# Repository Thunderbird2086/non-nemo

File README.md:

# 난네모
난네모 (Non Nemo) is an ortholinear 3x5 split keyboard. In Korean, 네모 (nemo) means 'rectangle,' and 난 (non) translates to 'I am.'  So, together, it brings the idea: 'I am a rectangle.'

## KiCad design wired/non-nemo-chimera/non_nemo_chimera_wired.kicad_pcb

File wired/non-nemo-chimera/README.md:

# 선달린 난네모 Chimera

## BOM
| **Component**        | **Quantity** | **Description**  |
|---                   |---:          |---               |
| Xiao RP2040          | 2            | MCU              |
| 1N4148W              | 36           | SMD 1206 SOD-123 |
| MX Hotswap sockets   | 30           | Hotswap sockets compatible with MX switches |
| MX Keyswitches       | 30           | MX compatible keyswitches |
| MX Key caps          | 30           | MX compatible keycaps |
| Choc Hotswap sockets | 6            | Hotswap sockets compatible with Choc switches |
| Choc Keyswitches     | 6            | Choc compatible keyswitches |
| Choc Key caps        | 6            | Choc compatible keycaps |
| PCB                  | 1            | MX Profile      |
| Tactile Push Button  | 2            | SMD 2x4x3.5mm    |
| top plate MX         | 1            | [Chimera](../plates/chimera/) |
| top plate            | 1            | [Chimera](../plates/chimera/) |
| bottom plate         | 1            | [Chimera](../plates/chimera/) |
| M2 screw	           | 32           | M2x5mm          |
| M2 spacer            | 16           | M2x5mm          |
| M2 standoff          | 10           | M2x3mm          |
| Rubber foot          | 8            | 8x3mm           |

## PCB

## Case
### Plates

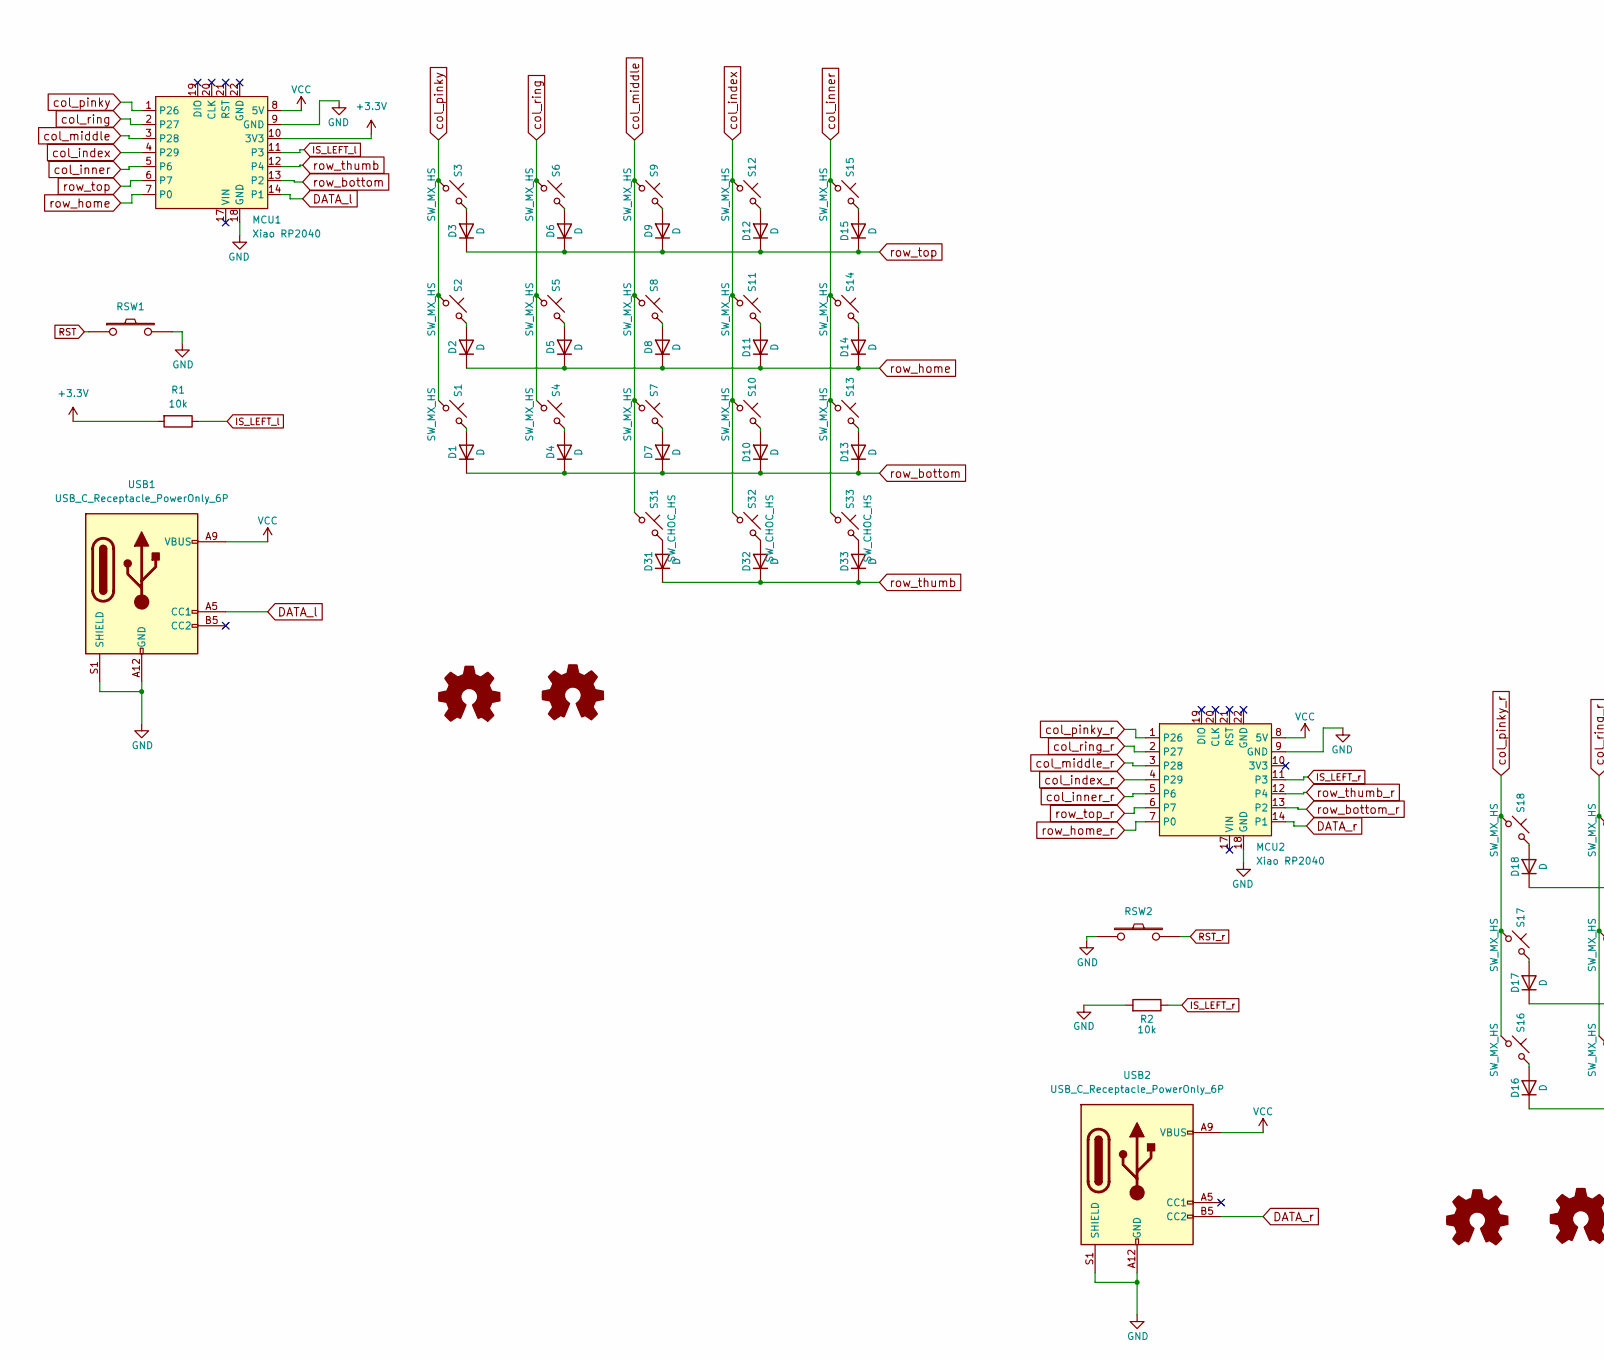
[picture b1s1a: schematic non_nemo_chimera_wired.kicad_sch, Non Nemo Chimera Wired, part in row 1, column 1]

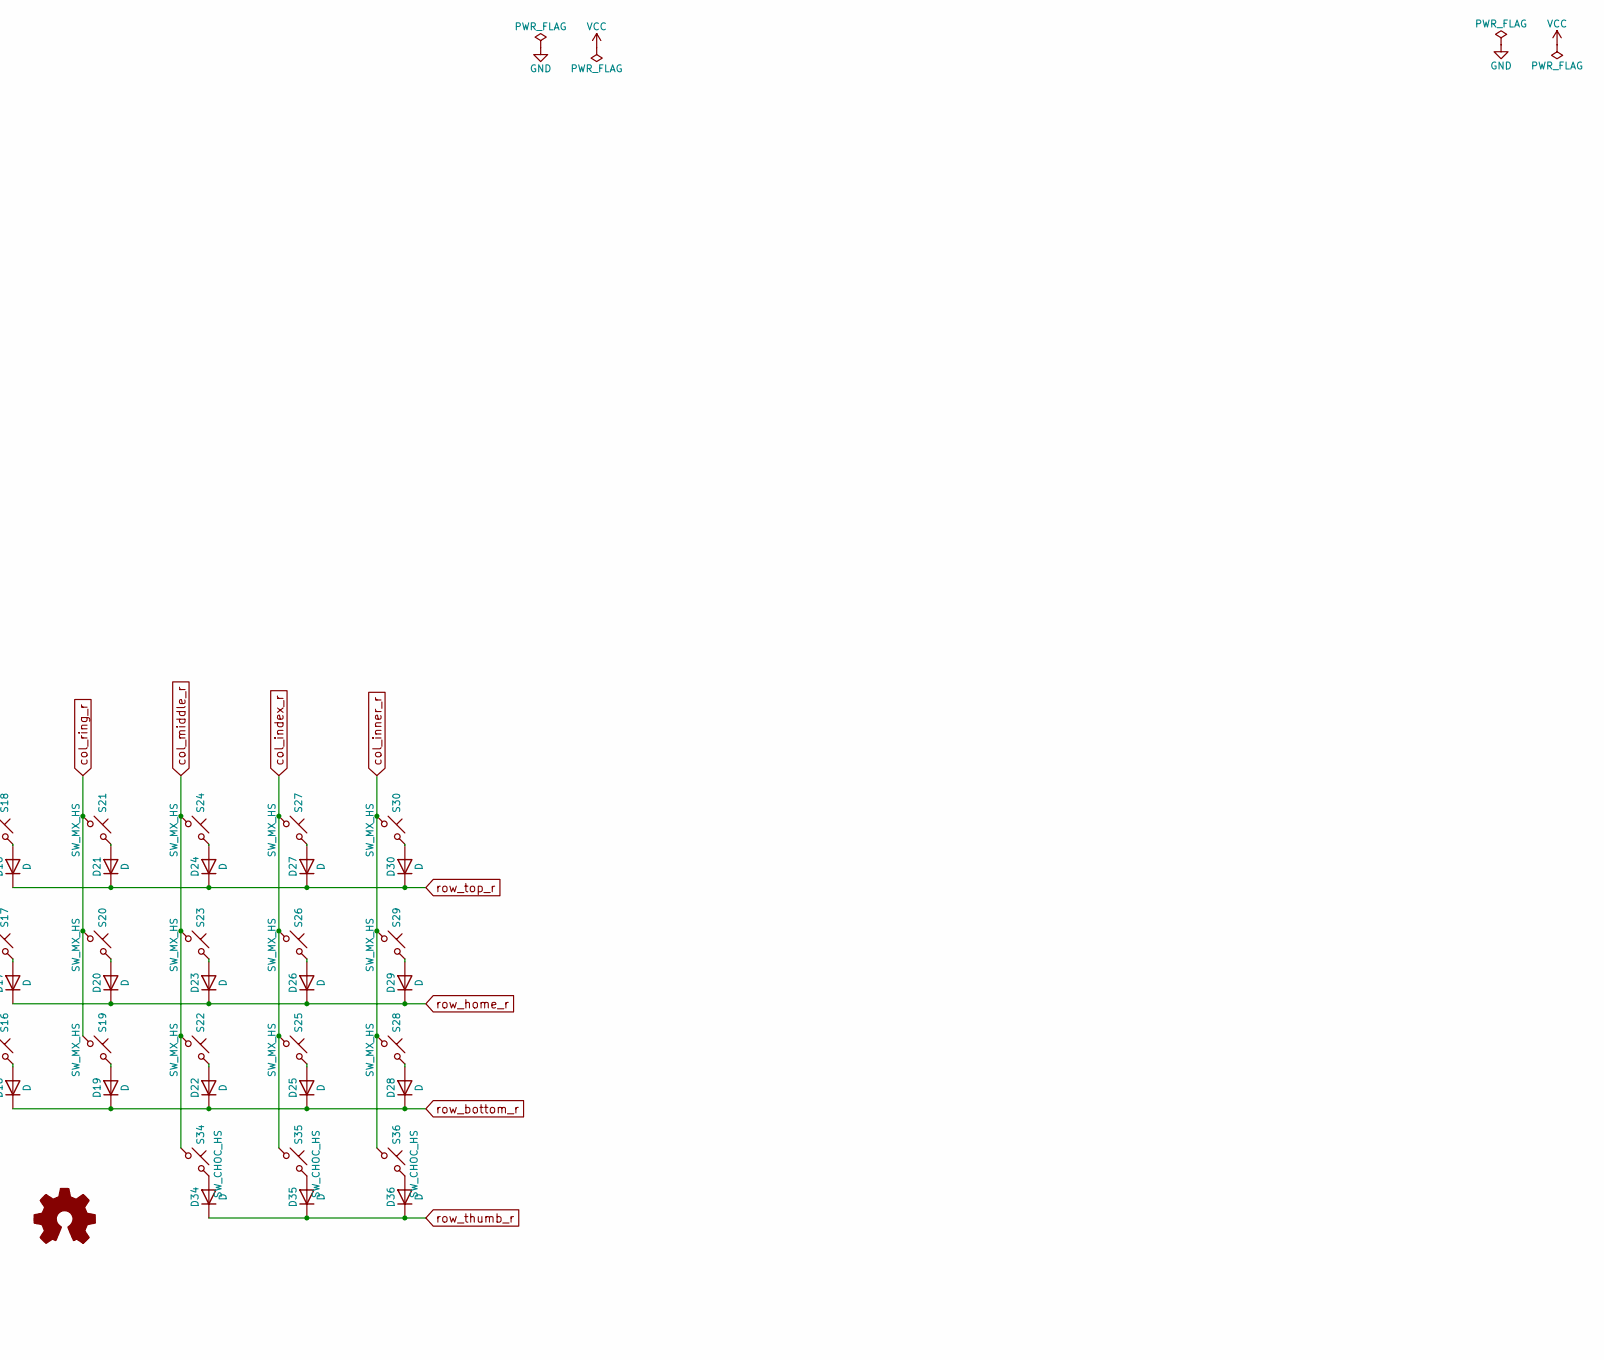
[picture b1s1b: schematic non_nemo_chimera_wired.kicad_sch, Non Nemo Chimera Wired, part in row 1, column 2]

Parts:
D1, D2, D3, D4, D5, D6, D7, D8, D9, D10, D11, D12, D13, D14, D15, D16, D17, D18, D19, D20, D21, D22, D23, D24, D25, D26, D27, D28, D29, D30, D31, D32, D33, D34, D35, D36: D; D3_SMD
LOGO1, LOGO3: Logo_Open_ErgoGen; utility_ergogen_logo
LOGO2, LOGO4: Logo_Open_Hardware_Small; OSHW-Logo_5.7x6mm_SilkScreen
MCU1, MCU2: Xiao RP2040; xiao_rp2040
R1, R2: 10k; R_0805_2012Metric_Pad1.20x1.40mm_HandSolder
RSW1, RSW2: SMT 2X4X3.5MM Tactile Tact Push Button
S1, S2, S3, S4, S5, S6, S7, S8, S9, S10, S11, S12, S13, S14, S15, S16, S17, S18, S19, S20, S21, S22, S23, S24, S25, S26, S27, S28, S29, S30: SW_MX_HS; SW_MX_HS_1u
S31, S32, S33, S34, S35, S36: SW_CHOC_HS; SW_choc_v1_v2_HS_1u
USB1, USB2: USB_C_Receptacle_PowerOnly_6P; USB-20C-F-6C16

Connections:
+3.3V: MCU1.10 (3V3), R1.2
DATA_l: MCU1.14 (P1), USB1.A5 (CC1)
DATA_r: MCU2.14 (P1), USB2.B5 (CC2)
GND: MCU1.9 (GND), MCU1.18 (GND), MCU2.9 (GND), MCU2.18 (GND), R2.2, RSW1.2, RSW2.1, USB1.A12 (GND), USB1.B12 (GND), USB1.S1 (SHIELD), USB2.A12 (GND), USB2.B12 (GND), USB2.S1 (SHIELD)
IS_LEFT_l: MCU1.11 (P3), R1.1
IS_LEFT_r: MCU2.11 (P3), R2.1
unnamed: D1.2 (A), S1.1
unnamed: D2.2 (A), S2.1
unnamed: D3.2 (A), S3.1
unnamed: D4.2 (A), S4.1
unnamed: D5.2 (A), S5.1
unnamed: D6.2 (A), S6.1
unnamed: D7.2 (A), S7.1
unnamed: D8.2 (A), S8.1
unnamed: D9.2 (A), S9.1
unnamed: D10.2 (A), S10.1
unnamed: D11.2 (A), S11.1
unnamed: D12.2 (A), S12.1
unnamed: D13.2 (A), S13.1
unnamed: D14.2 (A), S14.1
unnamed: D15.2 (A), S15.1
unnamed: D16.2 (A), S16.1
unnamed: D17.2 (A), S17.1
unnamed: D18.2 (A), S18.1
unnamed: D19.2 (A), S19.1
unnamed: D20.2 (A), S20.1
unnamed: D21.2 (A), S21.1
unnamed: D22.2 (A), S22.1
unnamed: D23.2 (A), S23.1
unnamed: D24.2 (A), S24.1
unnamed: D25.2 (A), S25.1
unnamed: D26.2 (A), S26.1
unnamed: D27.2 (A), S27.1
unnamed: D28.2 (A), S28.1
unnamed: D29.2 (A), S29.1
unnamed: D30.2 (A), S30.1
unnamed: D31.2 (A), S31.1
unnamed: D32.2 (A), S32.1
unnamed: D33.2 (A), S33.1
unnamed: D34.2 (A), S34.1
unnamed: D35.2 (A), S35.1
unnamed: D36.2 (A), S36.1
RST: RSW1.1
RST_r: RSW2.2
VCC: MCU1.8 (5V), MCU2.8 (5V), USB1.A9 (VBUS), USB1.B9 (VBUS), USB2.A9 (VBUS), USB2.B9 (VBUS)
col_index: MCU1.4 (P29), S10.2, S11.2, S12.2, S32.2
col_index_r: MCU2.4 (P29), S25.2, S26.2, S27.2, S35.2
col_inner: MCU1.5 (P6), S13.2, S14.2, S15.2, S33.2
col_inner_r: MCU2.5 (P6), S28.2, S29.2, S30.2, S36.2
col_middle: MCU1.3 (P28), S7.2, S8.2, S9.2, S31.2
col_middle_r: MCU2.3 (P28), S22.2, S23.2, S24.2, S34.2
col_pinky: MCU1.1 (P26), S1.2, S2.2, S3.2
col_pinky_r: MCU2.1 (P26), S16.2, S17.2, S18.2
col_ring: MCU1.2 (P27), S4.2, S5.2, S6.2
col_ring_r: MCU2.2 (P27), S19.2, S20.2, S21.2
row_bottom: D1.1 (K), D4.1 (K), D7.1 (K), D10.1 (K), D13.1 (K), MCU1.13 (P2)
row_bottom_r: D16.1 (K), D19.1 (K), D22.1 (K), D25.1 (K), D28.1 (K), MCU2.13 (P2)
row_home: D2.1 (K), D5.1 (K), D8.1 (K), D11.1 (K), D14.1 (K), MCU1.7 (P0)
row_home_r: D17.1 (K), D20.1 (K), D23.1 (K), D26.1 (K), D29.1 (K), MCU2.7 (P0)
row_thumb: D31.1 (K), D32.1 (K), D33.1 (K), MCU1.12 (P4)
row_thumb_r: D34.1 (K), D35.1 (K), D36.1 (K), MCU2.12 (P4)
row_top: D3.1 (K), D6.1 (K), D9.1 (K), D12.1 (K), D15.1 (K), MCU1.6 (P7)
row_top_r: D18.1 (K), D21.1 (K), D24.1 (K), D27.1 (K), D30.1 (K), MCU2.6 (P7)

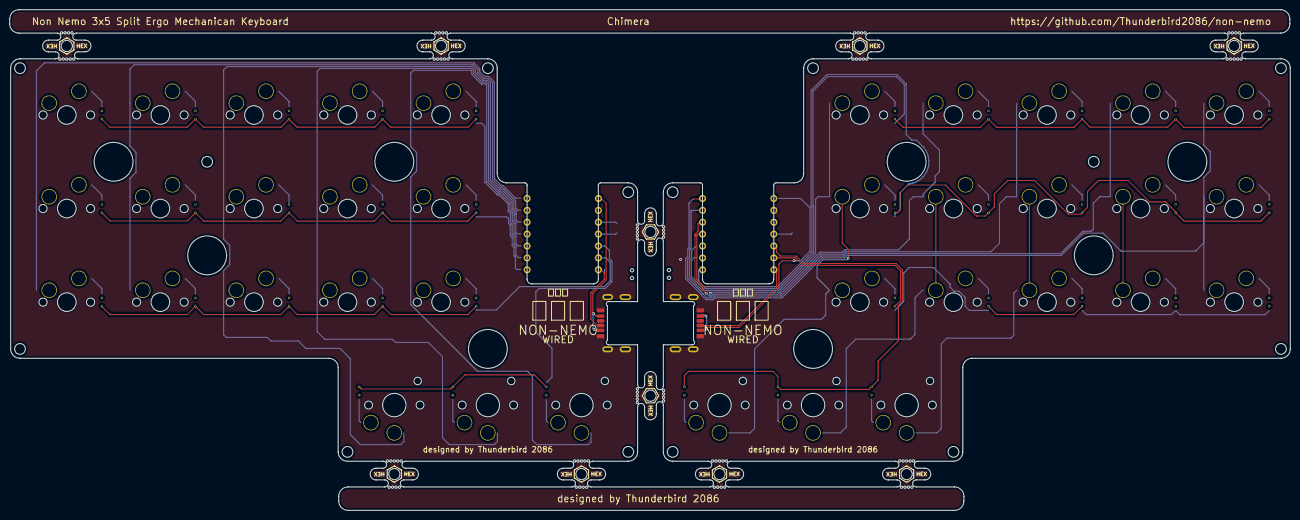
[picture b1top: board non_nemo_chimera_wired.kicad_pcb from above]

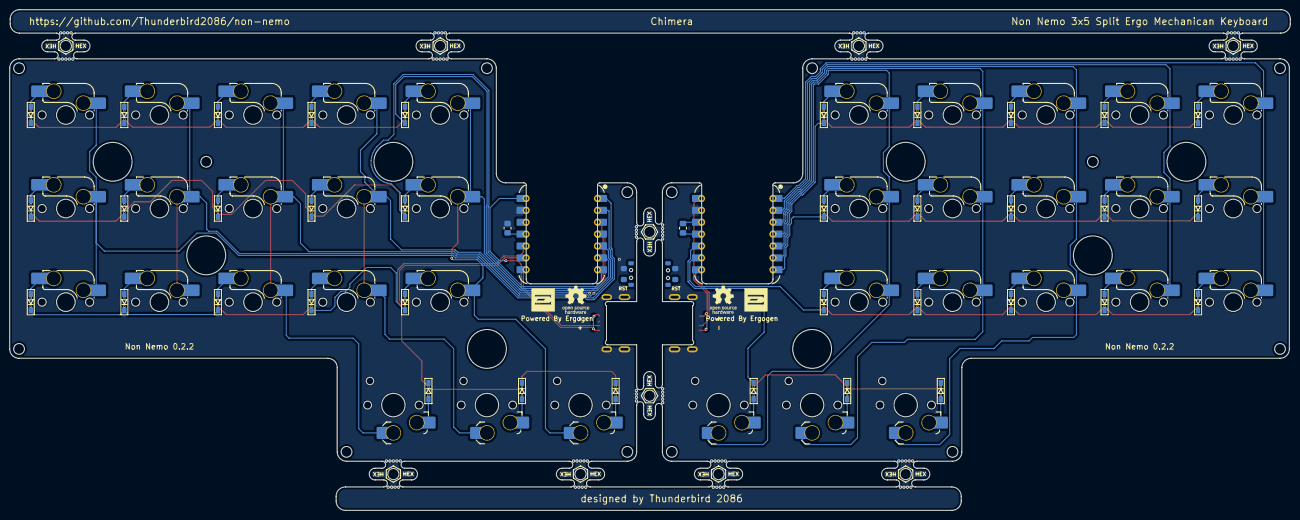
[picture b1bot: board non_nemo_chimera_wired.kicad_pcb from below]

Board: 2 copper layers, 273.7 x 107.0 mm, 94 parts (6 on the bottom side), 61 nets.

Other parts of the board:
X1, X2, X3, X4, X5, X6, X7, X8, X9, X10: 5.5mm; mousebites_5p5mm_easysnap

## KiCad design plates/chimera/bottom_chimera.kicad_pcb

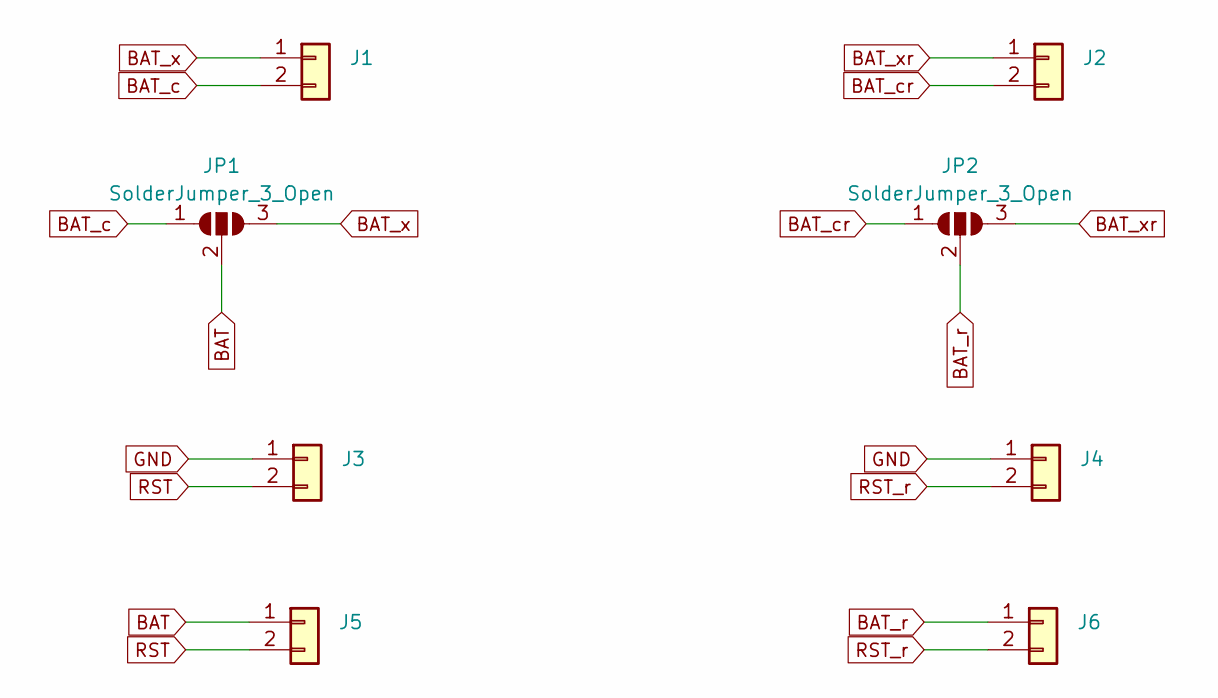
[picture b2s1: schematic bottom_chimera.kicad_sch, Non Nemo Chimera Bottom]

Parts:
J1, J2, J3, J4, J5, J6: Conn_01x02; Tag_Pogopin_1x02_P2.54mm
JP1, JP2: SolderJumper_3_Open

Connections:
BAT: J5.1, JP1.2 (C)
BAT_c: J1.2, JP1.1 (A)
BAT_cr: J2.2, JP2.1 (A)
BAT_r: J6.1, JP2.2 (C)
BAT_x: J1.1, JP1.3 (B)
BAT_xr: J2.1, JP2.3 (B)
GND: J3.1, J4.1
RST: J3.2, J5.2
RST_r: J4.2, J6.2

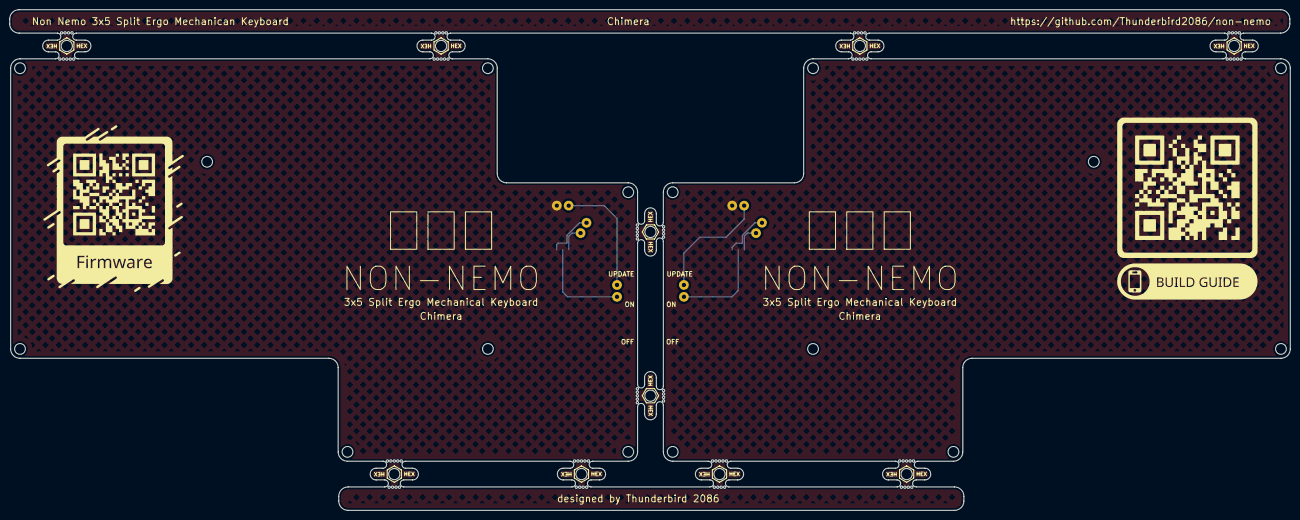
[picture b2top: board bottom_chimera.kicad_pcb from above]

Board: 2 copper layers, 273.7 x 107.0 mm, 18 parts (0 on the bottom side), 9 nets.

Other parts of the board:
X1, X2, X3, X4, X5, X6, X7, X8, X9, X10: 5.5mm; mousebites_5p5mm_easysnap

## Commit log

2025-04-04 ergogen
2025-04-05 updated ergogen
2025-04-05 ready for artwork
2025-04-05 refreshed submodule
2025-04-05 artwork
2025-04-05 dumped PCB images
2025-04-05 Low Profile (#1)
    * ergogen
    * updated ergogen
    * ready for artwork
    * refreshed submodule
    * artwork
    * dumped PCB images
2025-04-06 reorg directory
2025-04-06 small tweaks
2025-04-06 small changes (#2)
    * reorg directory
    * small tweaks
    * updated README.md
2025-04-06 updated README.md for low profile
2025-04-06 minor changes
2025-04-06 added MX Profile
2025-04-06 MX profile
2025-04-06 MX profile (#3)
    * updated README.md for low profile
    * minor changes
    * added MX Profile
    * MX profile
2025-04-06 updated MX bottom plate
2025-04-06 Chimera profile
2025-04-06 Chimera (#4)
    * updated MX bottom plate
    * Chimera profile
2025-04-07 added git workflow
2025-04-07 small tweak
2025-04-07 changed non_nemo to non_nemo_low
2025-04-07 git workflow
2025-04-07 tweaking git workflow
2025-04-07 git workflow for plates
2025-04-07 naming
2025-04-07 git workflow (#5)
    * added git workflow
    * small tweak
    * changed non_nemo to non_nemo_low
    * git workflow
    * tweaking git workflow
    * git workflow for plates
2025-04-09 added reset switch
2025-04-09 Low Profile
    pogopin and reset button
2025-04-09 MX Profile
    pogopin and reset switch
2025-04-09 MX Profile PCB
2025-04-09 Chimera
    pogopin and reset switch
2025-04-09 version
2025-04-09 reset switch (#6)
    * added reset switch
    * Low Profile
    pogopin and reset button
    * MX Profile
    pogopin and reset switch
    * MX Profile PCB
2025-04-13 added shells for chimera
2025-04-13 added shells for low profile
2025-04-13 added shells for mx profile
2025-04-13 Shells (#7)
    * added shells for chimera
    * added shells for low profile
    * added shells for mx profile
2025-04-18 fixed footprint layer for Chimera
2025-04-18 fixed footprint layer for low
2025-04-18 fixed footprint layer for mx
2025-04-20 added wired version of chimera
2025-04-20 added wired version of chimera (#9)
2025-04-21 Updated cases for Chimera Wired
2025-04-21 updated README.md for Chimera Wired
2025-04-21 updated github workflow
2025-04-21 Chimera Wired + Case (#10)
    * Updated cases for Chimera Wired
    * updated README.md for Chimera Wired
    * updated github workflow
2025-04-27 updated cases for Non Nemo Wired
2025-04-29 reorg directory structure
2025-05-01 added standoff holes for case
    Non Nemo Chimera Wireless
2025-05-03 updated cases for Chimera for wired and wireless
2025-05-03 updated README.md (#11)
    * updated cases for Non Nemo Wired
    * reorg directory structure
    * added standoff holes for case
    Non Nemo Chimera Wireless
    * updated README.md
    * updated github workflow
2025-05-10 fixed Non Nemo Wired
2025-05-10 fixed ergogen for Wired
2025-05-10 fixed Wired (#12)
    * fixed Non Nemo Wired
    * fixed ergogen for Wired
2025-06-15 updated case for wireless
    * only for Chimera for now
2025-06-15 updated case for wireless (#13)
    * only for Chimera for now
